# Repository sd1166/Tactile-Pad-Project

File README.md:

# Tactile

## Build

Requires Python 3.10+. From the repo root:

```bash
python -m venv .venv
source .venv/bin/activate   # Windows: .venv\Scripts\activate
pip install -r requirements.txt
```

## Run

```bash
python app.py
```

(or `python -m tactile`)

The app expects a Pico on USB with `PICO_SERIAL_PORT` if the default device is wrong.

## WS2812 panel (Display)

Flash `pico/pico_ws2812_receiver.py` as `main.py` on the Pico. Data in to **GP12** (edit `PIN_DATA` in that file if your DIN uses another pin). Use a solid **5 V** supply for the matrix; common ground with the Pico.

**Reference panel:** the same **32×8** class as Adafruit `NeoMatrix(32, 8, PIN, NEO_MATRIX_BOTTOM + NEO_MATRIX_RIGHT + NEO_MATRIX_COLUMNS + NEO_MATRIX_ZIGZAG, NEO_GRB + NEO_KHZ800)`. This repo’s **defaults** match the **layout** part of that line (not the pin or color flags):

| Adafruit | Env (default in parentheses) |
|----------|------------------------------|
| `32`, `8` | Logical grid 32×8 (fixed in host + Pico frame size) |
| `NEO_MATRIX_COLUMNS` | **`WS2812_COLUMN_MAJOR=1`** (default **on**) |
| `NEO_MATRIX_ZIGZAG` | **`WS2812_SERPENTINE=1`** (default **on**) |
| Native 32×8 strip order (not treating the chain as 8×32) | **`WS2812_SWAP_AXES=0`** (default **off**) |
| `NEO_MATRIX_BOTTOM` + `NEO_MATRIX_RIGHT` | Tune **`WS2812_FLIP_X`** / **`WS2812_FLIP_Y`** until a letter and `ws2812_diag.py compare` look correct (no single env line equals both flags) |
| `NEO_GRB` | MicroPython `neopixel` on the Pico usually matches WS2812 **GRB** when you set `(R, G, B)` tuples; if red and green swap, fix in firmware or host byte order |

**Strip layout (env):**

- **`WS2812_SWAP_AXES`** (default **off**): **on** (`1`) when the physical chain is wired as **8×32** but you still draw **32×8** Braille; maps logical `(x,y)` to `(y,x)` on an 8×32 index grid. **off** matches **`NeoMatrix(32, 8, …)`**-style **32×8** order.
- **`WS2812_COLUMN_MAJOR`** (default **on**): column-first strip order (same idea as **`NEO_MATRIX_COLUMNS`**). Set to **`0`** for row-major panels.
- **`WS2812_SERPENTINE`** (default **on**): zig-zag along the active dimension (columns when column-major). Set **`0`** if `ws2812_diag.py compare` pattern A only looks right.
- **`WS2812_FLIP_X`**, **`WS2812_FLIP_Y`** (default **off** / **on**): mirror in strip space after swap. Adjust if text is mirrored or upside down relative to your DIN corner.

### Connection and wiring checks

From the repo root (with the Pico unplugged from Thonny and `PICO_SERIAL_PORT` set if needed):

```bash
python scripts/ws2812_diag.py solid red
python scripts/ws2812_diag.py compare
python scripts/ws2812_diag.py clear
```

`solid red` (or `white`) proves USB + firmware are receiving frames. If the Pico runs `pico_ws2812_receiver.py`, you should also see **`frame ok bytes 768`** in the script output when the Pico prints to USB. **`compare`** shows horizontal stripes twice (serpentine off, then on) so you can pick **`WS2812_SERPENTINE`**; **`stripes`** uses the same mapping as the running app (including env).

### Nothing lights up

- **One letter** (for example `a`) only turns on **one** LED at the top-left of the logical grid. It is easy to miss or to land on a dead pixel; try a short word like `hello`.
- If horizontal bands from `ws2812_diag.py compare` look broken, use the script’s A/B hint for `WS2812_SERPENTINE`, then adjust `WS2812_SWAP_AXES`, `WS2812_FLIP_X`, `WS2812_FLIP_Y`, and `WS2812_COLUMN_MAJOR` (see above).
- If the Pico’s **green LED blinks** after each Display, the frame was received; the issue is then wiring, power, data pin, or `NEO_TIMING` in `pico_ws2812_receiver.py` (try `NEO_TIMING = 0`).
- Optional env: `WS2812_MARGIN_X`, `WS2812_MARGIN_Y` shift the pattern (pixels). `PICO_SERIAL_STARTUP_SEC` (default 3) waits after opening USB. `WS2812_POST_WRITE_DELAY_SEC` (default 0.06) pauses after each frame.
- **`WS2812_BRIGHTNESS`** (default `0.25`): scale for lit Braille pixels and `ws2812_diag` solids (0.0–1.0). Use `1.0` for full brightness.

### `frame ok bytes 768` but the matrix stays dark

Software and USB are fine; the problem is between **GP12** (or whatever `PIN_DATA` is) and the first LED.

1. **Power**  
   - **5 V** and **GND** from a supply that can deliver enough current for the whole matrix (not from the Pico 3.3 V pin).  
   - **Common ground**: strip GND must connect to **Pico GND** (same supply return path).

2. **Data wire**  
   - Panel **DIN** (first pixel data in) must go to the same GPIO as **`PIN_DATA`** in `pico_ws2812_receiver.py` (default **GP12**).

3. **Logic level**  
   - Pico outputs **3.3 V**. Many WS2812 strips need **5 V logic** on DIN. Use a **level shifter** (for example 74AHCT125) between that GPIO and DIN if the strip is picky.

4. **NeoPixel timing**  
   - On the Pico, in `pico_ws2812_receiver.py`, set **`NEO_TIMING = 0`** instead of `1`, save as `main.py`, reset, and run `python scripts/ws2812_diag.py solid red` again.

5. **Bypass USB (pure hardware test)**  
   This lights only **LED 0** on the strip with both timing values (no Flask, no base64):

   ```bash
   mpremote connect /dev/cu.usbmodem101 run pico/hw_smoke_ws2812.py
   ```

   If **still nothing**, wiring or power is wrong, or DIN is not the input of the first pixel you think it is. If **LED 0 blinks** but the full panel test stays dark, suspect a very long strip, a bad first LED, or wrong `N` (256) for your actual layout (still, LED 0 should react).

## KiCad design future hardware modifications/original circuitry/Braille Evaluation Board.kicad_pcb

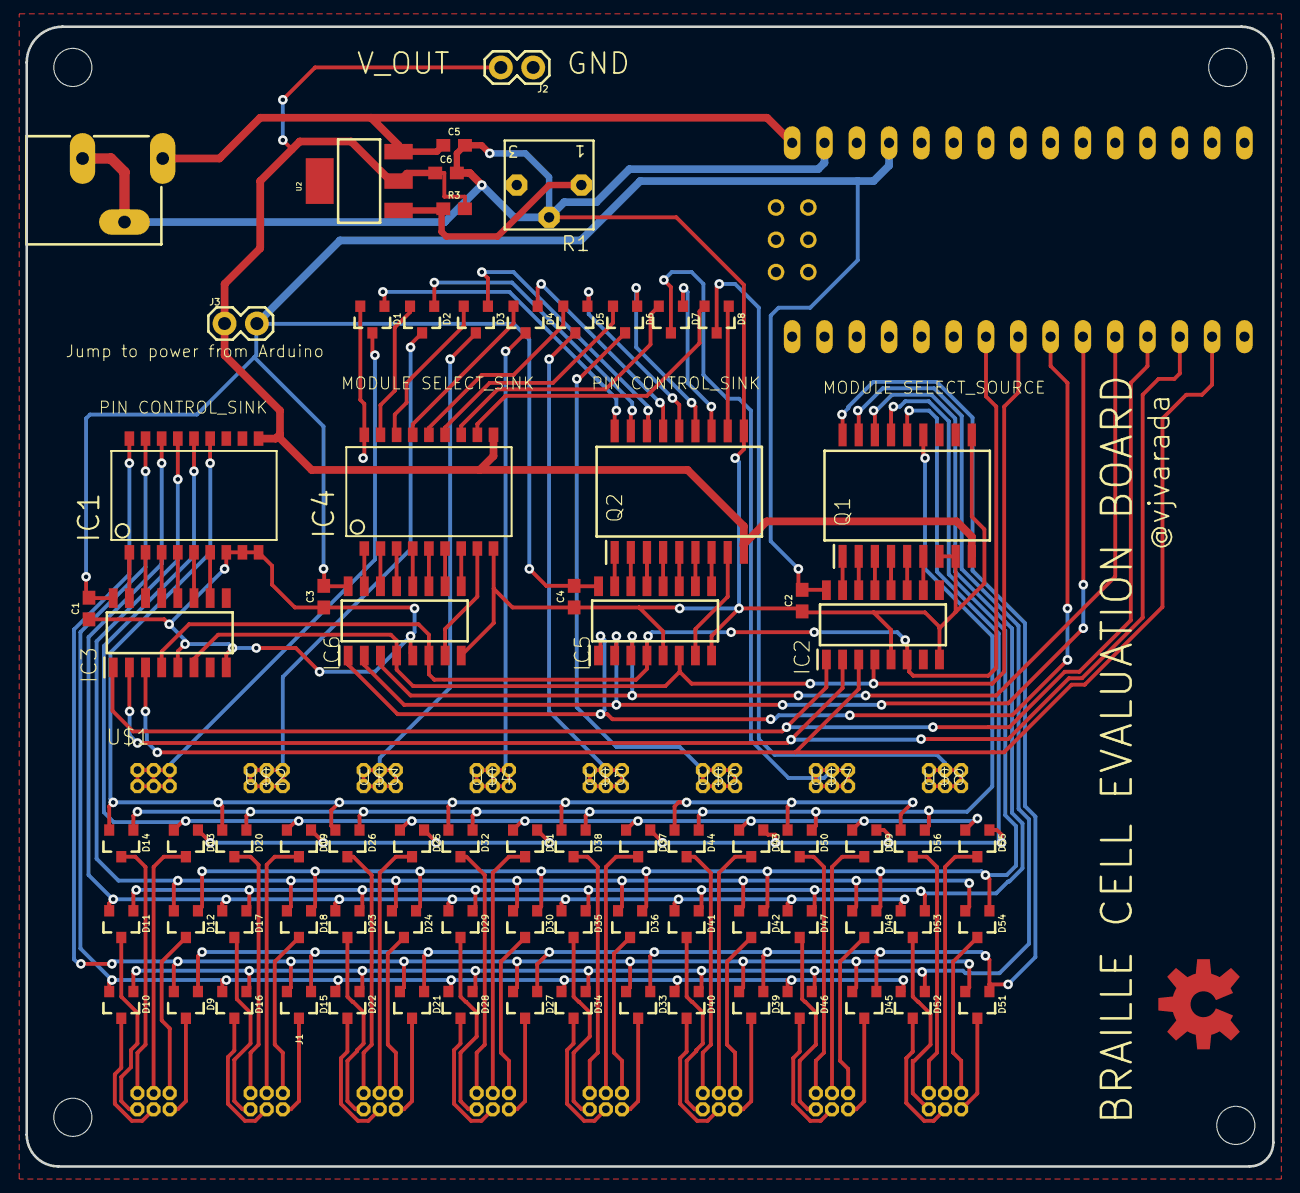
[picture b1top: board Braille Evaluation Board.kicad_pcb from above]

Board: 2 copper layers, 98.0 x 89.6 mm, 90 parts (0 on the bottom side), 125 nets.

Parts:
C1, C2, C3, C4, C5: 0.1uF; 0603
C6: 1uf; 0603
D1, D2, D3, D4, D5, D6, D7, D8, D9, D10, D11, D12, D13, D14, D15, D16, D17, D18, D19, D20, D21, D22, D23, D24, D25, D26, D27, D28, D29, D30, D31, D32, D33, D34, D35, D36, D37, D38, D39, D40, D41, D42, D43, D44, D45, D46, D47, D48, D49, D50, D51, D52, D53, D54, D55, D56: 200mA/70V; SOT23-3
IC1, IC4: TD62083; SO18
IC2, IC3, IC5, IC6: 74HC238D; SOIC127P600X175-16N
J1: POWER_JACKSLT; POWER_JACK_SLOT
J2, J3: 1X02
LOGO1: OSHW-LOGOL-COPPER; OSHW-LOGO-L_COPPER
Q1, Q2: TBD62783AFG,EL; SOIC127P1030X245-18N
R1: 3362P
R3: 240R; 0603
U2: LM317; SOT223
U$1, U$2, U$3, U$4, U$5, U$6, U$7, U$8: BRAILLE-6
U$9: NANO
UNK_HOLE_0: dummyfp0
UNK_HOLE_1: dummyfp1
UNK_HOLE_2: dummyfp2
UNK_HOLE_3: dummyfp3

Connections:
GND: C1.1, C2.1, C3.1, C4.1, C5.2, C6.2, IC1.7, IC1.8, IC1.9, IC2.5, IC2.8, IC3.5, IC3.8, IC4.9, IC5.5, IC5.8, IC6.5, IC6.8, J1.GND@1, J1.GND@2, J2.1, Q1.7, Q1.8, Q1.10, Q2.10, R1.2, U$9.GND
MOD_0: IC5.1, IC6.1, U$9.D6
MOD_1: IC5.2, IC6.2, U$9.D7
MOD_2: IC5.3, IC6.3, U$9.D8
unnamed: IC2.15, Q1.1
unnamed: IC2.14, Q1.2
unnamed: IC2.13, Q1.3
unnamed: IC2.12, Q1.4
unnamed: IC2.11, Q1.5
unnamed: IC2.10, Q1.6
unnamed: IC1.1, IC3.15
unnamed: IC1.2, IC3.14
unnamed: IC1.3, IC3.13
unnamed: IC1.4, IC3.12
unnamed: IC1.5, IC3.11
unnamed: IC5.15, Q2.1
unnamed: IC5.14, Q2.2
unnamed: IC5.13, Q2.3
unnamed: IC5.12, Q2.4
unnamed: IC5.11, Q2.5
unnamed: D1.1, Q2.18
unnamed: IC4.1, IC6.15
unnamed: IC4.2, IC6.14
unnamed: IC4.3, IC6.13
unnamed: IC4.4, IC6.12
unnamed: IC4.5, IC6.11
unnamed: D2.1, Q2.17
unnamed: IC5.10, Q2.6
unnamed: D3.1, Q2.16
unnamed: IC5.9, Q2.7
unnamed: IC5.7, Q2.8
unnamed: IC4.8, IC6.7
unnamed: IC4.6, IC6.10
unnamed: IC4.7, IC6.9
unnamed: D4.1, Q2.15
unnamed: IC1.6, IC3.10
unnamed: D5.1, Q2.14
unnamed: D6.1, Q2.13
unnamed: D7.1, Q2.12
unnamed: D8.1, Q2.11
unnamed: D1.2, IC4.18
unnamed: D9.3, U$1.P$2
unnamed: D2.2, IC4.17
unnamed: D3.3, U$3.P$1, U$3.P$3, U$3.P$5, U$3.P$7, U$3.P$9, U$3.P$11
unnamed: D4.3, U$4.P$1, U$4.P$3, U$4.P$5, U$4.P$7, U$4.P$9, U$4.P$11
unnamed: D5.3, U$5.P$1, U$5.P$3, U$5.P$5, U$5.P$7, U$5.P$9, U$5.P$11
unnamed: D6.3, U$6.P$1, U$6.P$3, U$6.P$5, U$6.P$7, U$6.P$9, U$6.P$11
unnamed: D7.3, U$7.P$1, U$7.P$3, U$7.P$5, U$7.P$7, U$7.P$9, U$7.P$11
unnamed: D8.3, U$8.P$1, U$8.P$3, U$8.P$5, U$8.P$7, U$8.P$9, U$8.P$11
unnamed: D10.3, U$1.P$4
unnamed: D11.3, U$1.P$6
unnamed: D12.3, U$1.P$8
unnamed: D13.3, U$1.P$10
unnamed: D14.3, U$1.P$12
unnamed: D21.3, U$3.P$2
unnamed: D10.1, D16.1, D22.1, D28.1, D34.1, D40.1, D46.1, D52.1, Q1.17
unnamed: D11.1, D17.1, D23.1, D29.1, D35.1, D41.1, D47.1, D53.1, Q1.16
unnamed: D12.1, D18.1, D24.1, D30.1, D36.1, D42.1, D48.1, D54.1, Q1.15
unnamed: D27.3, U$4.P$2
unnamed: D33.3, U$5.P$2
unnamed: D9.2, D15.2, D21.2, D27.2, D33.2, D39.2, D45.2, D51.2, IC1.18
unnamed: D39.3, U$6.P$2
unnamed: D11.2, D17.2, D23.2, D29.2, D35.2, D41.2, D47.2, D53.2, IC1.16
unnamed: D12.2, D18.2, D24.2, D30.2, D36.2, D42.2, D48.2, D54.2, IC1.15
unnamed: D13.2, D19.2, D25.2, D31.2, D37.2, D43.2, D49.2, D55.2, IC1.14
unnamed: D14.2, D20.2, D26.2, D32.2, D38.2, D44.2, D50.2, D56.2, IC1.13
unnamed: D15.3, U$2.P$2
unnamed: D16.3, U$2.P$4
unnamed: D17.3, U$2.P$6
unnamed: D18.3, U$2.P$8
unnamed: D19.3, U$2.P$10
unnamed: D20.3, U$2.P$12
unnamed: D28.3, U$4.P$4
unnamed: D22.3, U$3.P$4
unnamed: D23.3, U$3.P$6
unnamed: D24.3, U$3.P$8
unnamed: D25.3, U$3.P$10
unnamed: D26.3, U$3.P$12
unnamed: D45.3, U$7.P$2
unnamed: D10.2, D16.2, D22.2, D28.2, D34.2, D40.2, D46.2, D52.2, IC1.17
unnamed: D51.3, U$8.P$2
unnamed: D1.3, U$1.P$1, U$1.P$3, U$1.P$5, U$1.P$7, U$1.P$9, U$1.P$11
unnamed: D2.3, U$2.P$1, U$2.P$3, U$2.P$5, U$2.P$7, U$2.P$9, U$2.P$11
unnamed: D29.3, U$4.P$6
unnamed: D30.3, U$4.P$8
unnamed: D3.2, IC4.16
unnamed: D13.1, D19.1, D25.1, D31.1, D37.1, D43.1, D49.1, D55.1, Q1.14
unnamed: D14.1, D20.1, D26.1, D32.1, D38.1, D44.1, D50.1, D56.1, Q1.13
unnamed: D4.2, IC4.15
unnamed: D5.2, IC4.14
unnamed: D6.2, IC4.13
unnamed: D7.2, IC4.12
unnamed: D8.2, IC4.11
unnamed: D31.3, U$4.P$10
unnamed: D32.3, U$4.P$12
unnamed: R1.1, R3.1, U2.1
unnamed: D34.3, U$5.P$4
unnamed: D35.3, U$5.P$6
unnamed: D36.3, U$5.P$8
unnamed: D37.3, U$5.P$10
unnamed: D38.3, U$5.P$12
unnamed: D40.3, U$6.P$4
unnamed: D41.3, U$6.P$6
unnamed: D42.3, U$6.P$8
unnamed: D43.3, U$6.P$10
unnamed: D44.3, U$6.P$12
unnamed: D46.3, U$7.P$4
unnamed: D47.3, U$7.P$6
unnamed: D48.3, U$7.P$8
unnamed: D49.3, U$7.P$10
unnamed: D50.3, U$7.P$12
unnamed: D52.3, U$8.P$4
unnamed: D53.3, U$8.P$6
unnamed: D54.3, U$8.P$8
unnamed: D55.3, U$8.P$10
unnamed: D56.3, U$8.P$12
unnamed: D9.1, D15.1, D21.1, D27.1, D33.1, D39.1, D45.1, D51.1, Q1.18
PIN_0: IC2.1, IC3.1, U$9.D9
PIN_1: IC2.2, IC3.2, U$9.D10
PIN_2: IC2.3, IC3.3, U$9.D11
RAW: C5.1, J1.PWR, U2.3, U$9.RAW
RESET: IC2.6, IC3.4, IC5.4, IC6.6, U$9.D4
SET: IC2.4, IC3.6, IC5.6, IC6.4, U$9.D5
VCC: C1.2, C2.2, C3.2, C4.2, IC2.16, IC3.16, IC5.16, IC6.16, J3.2, U$9.5V
V_DRIVE: C6.1, IC1.10, IC4.10, J2.2, J3.1, Q1.9, Q2.9, R3.2, U2.2

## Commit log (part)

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2026-03-23 add image_mapping folder
2026-03-23 image UI
2026-03-24 image conversion failed revision
2026-03-24 convert the image to 0 or 1
2026-03-25 file structure
2026-03-31 v2.0
2026-03-31 v2.1
2026-04-16 add in proto braille firmware file
2026-04-16 add LEDboard
2026-04-16 led_board update, server code
2026-04-16 server code in new file
2026-04-16 clean LEDboard a lil
2026-04-17 removed server code from ledboard file
2026-04-21 adding functionality
2026-04-21 refactoring code
2026-04-24 LED matrix additions
2026-04-28 demo text test prototype
2026-04-30 image update
2026-05-01 change from white to red to limit power
2026-05-01 accepting image logic in firmware backend
2026-05-01 logic edits
2026-05-01 fixed image resize issue
